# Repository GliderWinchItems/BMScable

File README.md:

# BMScable
Battery Management System cable tester.

Based on the ST's Nucleo 446R, this unit tests the battery module cable connector and wiring for correct voltages before using it with the BMS unit.

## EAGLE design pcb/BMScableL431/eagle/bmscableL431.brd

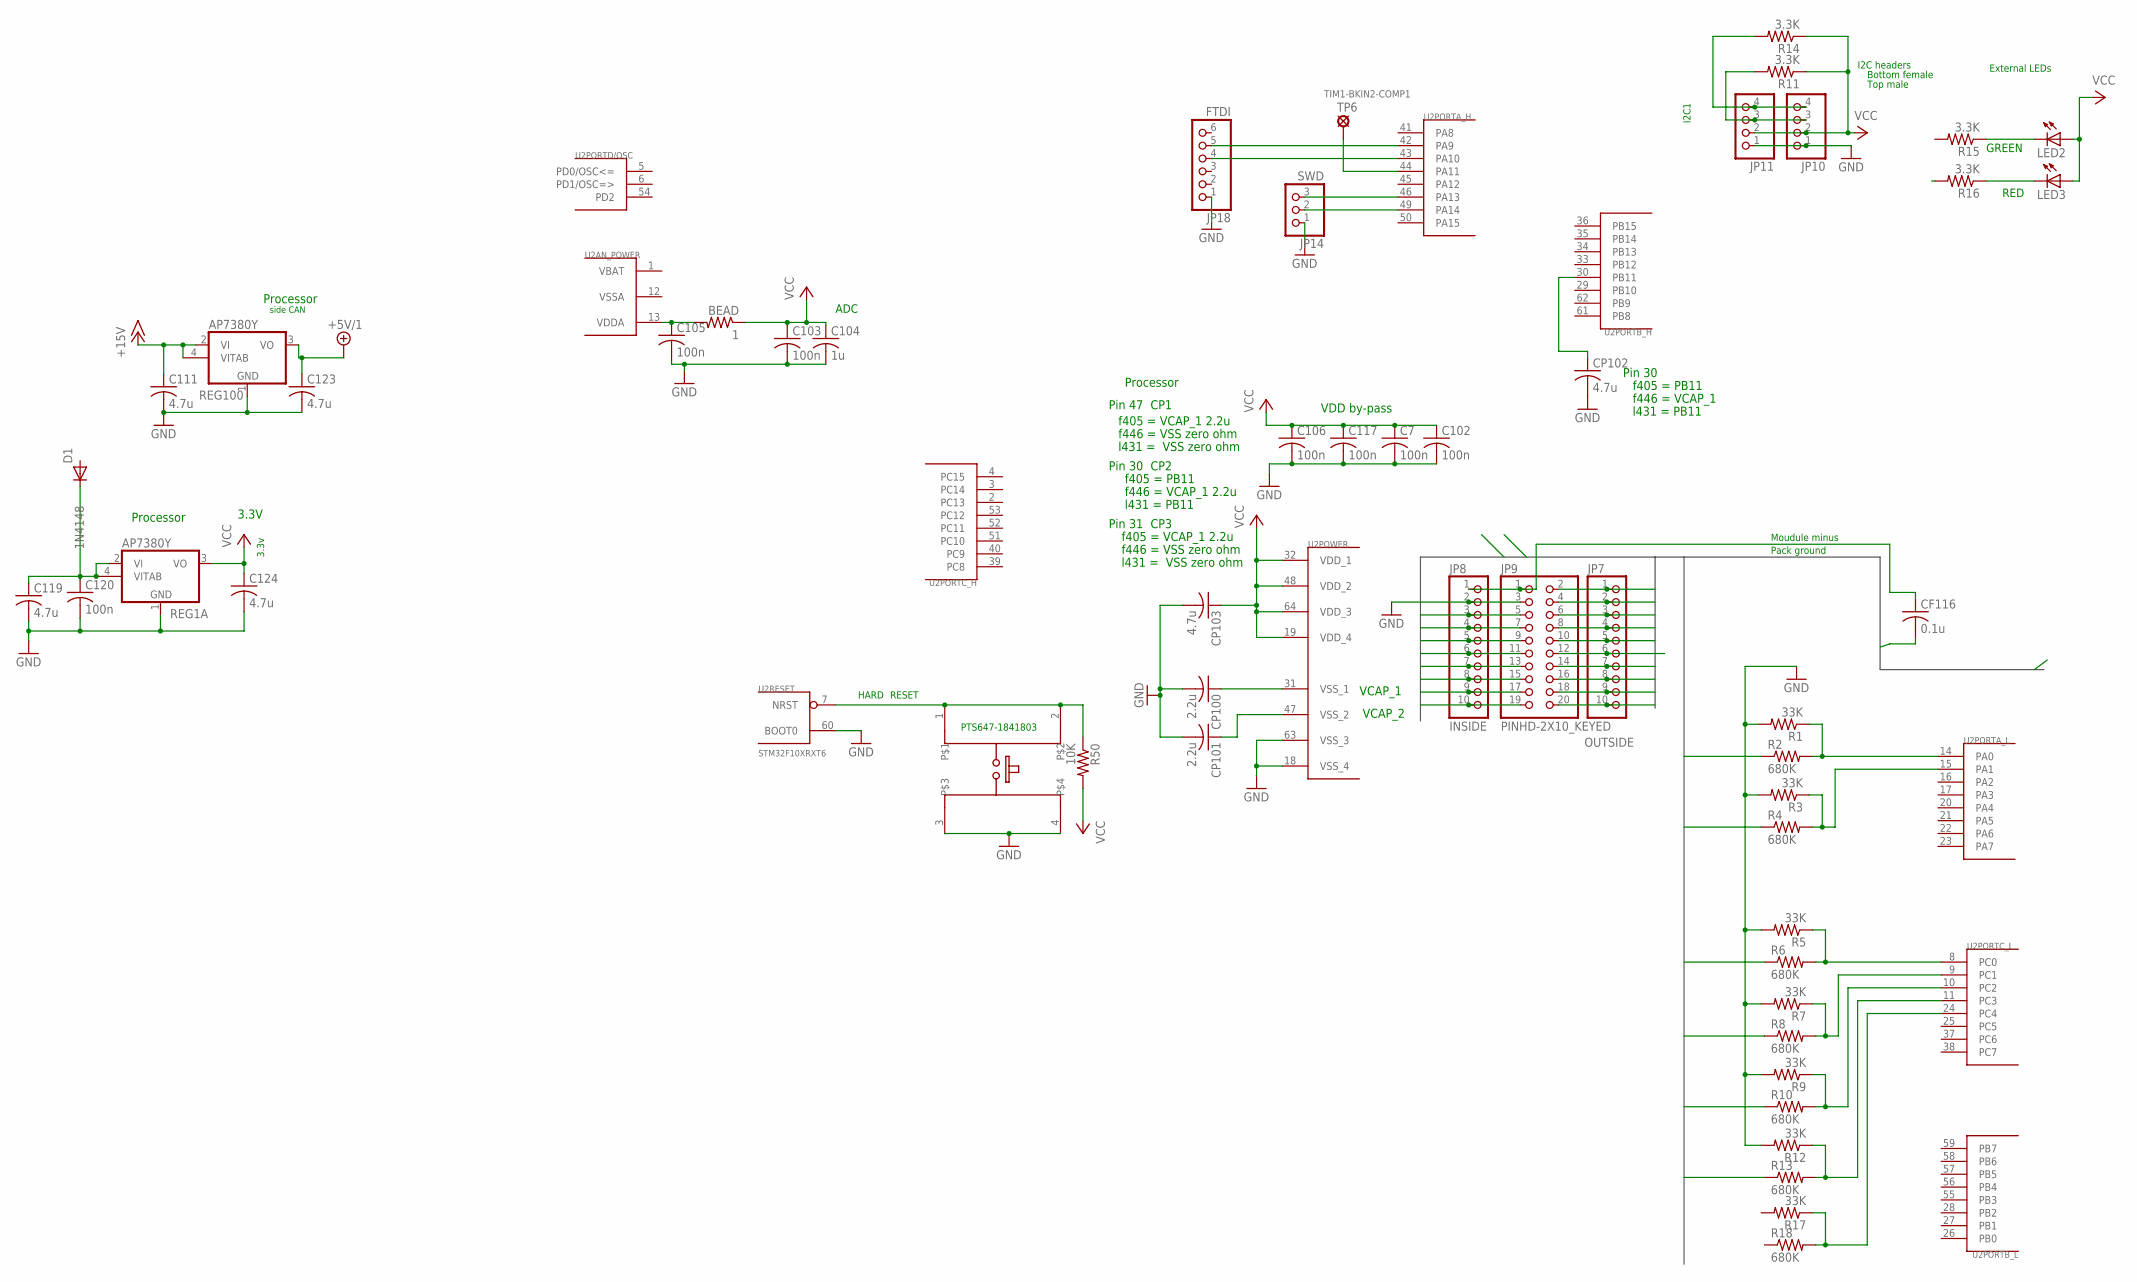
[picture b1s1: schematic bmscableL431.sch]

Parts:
BEAD: 1; R0603
C7, C102, C103, C105, C106, C117, C120: 100n; C0603
C104: 1u; C0603
C111, C119, C123: 4.7u; C0603
C124: 4.7u; C0805
CF116: 0.1u; C0603
CP100, CP101: 2.2u; C0603
CP102, CP103: 4.7u; C0603
D1: 1N4148; DO41-10_VERT
JP7: OUTSIDE; 1X10
JP8: INSIDE; 1X10
JP9: PINHD-2X10_KEYED; 2X10_KEYED
JP10, JP11: PINHD-1X4; 1X04
JP14: SWD; 1X03
JP18: FTDI; 1X06
LED2, LED3: LEDCHIP-LED0603; CHIP-LED0603
R1, R3, R5, R7, R9, R12, R17: 33K; R0603
R2, R4, R6, R8, R10, R13, R18: 680K; R0603
R11, R14, R15, R16: 3.3K; R0603
R50: 10K; R0603
REG1A, REG100: AP7380Y; SOT89
TP6: SOLDPAD0.6MM; SOLPAD.6MM
U2: STM32F10XRXT6; TQFP64
U$1: E-SWITCH2

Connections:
+5V/1: C123.1, REG100.3 (VO)
+15V: C111.1, REG100.2 (VI), REG100.4 (VITAB)
C0: JP7.2, JP9.4
C1: JP8.7, JP9.13
C2: JP8.3, JP9.5
C3: JP7.7, JP9.14, R4.1
C4: JP7.3, JP9.6
C5: JP8.8, JP9.15, R2.1
C6: JP8.4, JP9.7
C7: JP7.8, JP9.16, R13.1
C8: JP7.4, JP9.8
C9: JP8.9, JP9.17, R10.1
C10: JP8.5, JP9.9
C11: JP7.9, JP9.18, R8.1
C12: JP7.5, JP9.10
C13: JP8.10, JP9.19, R6.1
C14: JP8.6, JP9.11
C15: JP7.10, JP9.20
C16: JP7.6, JP9.12
GND: C7.2, C102.2, C103.2, C104.2, C105.2, C106.2, C111.2, C117.2, C119.2, C120.2, C123.2, C124.2, CP100.2, CP101.2, CP102.2, CP103.2, JP8.2, JP9.3, JP10.1, JP11.1, JP14.1, JP18.1, R1.2, R3.2, R5.2, R7.2, R9.2, R12.2, REG1A.1 (GND), REG100.1 (GND), U2.18 (VSS_4), U2.60 (BOOT0), U2.63 (VSS_3), U$1.3, U$1.4
LED-EXT-GRN-CATHODE: LED2.C, R15.1
LED-EXT-RED-CATHODE: LED3.C, R16.1
NRST: R50.1, U2.7 (NRST), U$1.1, U$1.2
PA0-C5-IN5: R1.1, R2.2, U2.14 (PA0)
PA1-C3-IN6: R3.1, R4.2, U2.15 (PA1)
PA9-USART1-TX: JP18.5, U2.42 (PA9)
PA10-USART1-RX: JP18.4, U2.43 (PA10)
PA13-SWDIO: JP14.3, U2.46 (PA13)
PA14-SWCLK: JP14.2, U2.49 (PA14)
PB1-LED-RED: R16.2
PB6-I2C1-SCL: JP10.4, JP11.4, R14.2
PB7-I2C2-SDA: JP10.3, JP11.3, R11.2
PB11-I2C2-SDA|VCAP1: CP102.1, U2.30 (PB11)
PC0-C13-IN1: R5.1, R6.2, U2.8 (PC0)
PC1-C11-IN2: R7.1, R8.2, U2.9 (PC1)
PC2-C9-IN3: R9.1, R10.2, U2.10 (PC2)
PC3-C7-IN4: R12.1, R13.2, U2.11 (PC3)
PC4-CX-IN13: R17.1, R18.2, U2.24 (PC4)
PGND_SRN_V: CF116.1, JP8.1, JP9.1
SRP: CF116.2, JP7.1, JP9.2
TIM1_BKIN2_COMP2: TP6.MP, U2.44 (PA11)
V-ORED: C119.1, C120.1, D1.C, REG1A.2 (VI), REG1A.4 (VITAB)
VBAT: U2.1 (VBAT)
VCC: BEAD.1, C7.1, C102.1, C103.1, C104.1, C106.1, C117.1, C124.1, CP103.1, JP10.2, JP11.2, LED2.A, LED3.A, R11.1, R14.1, R50.2, REG1A.3 (VO), U2.19 (VDD_4), U2.32 (VDD_1), U2.48 (VDD_2), U2.64 (VDD_3)
VDDA1: BEAD.2, C105.1, U2.13 (VDDA)
VSSA: U2.12 (VSSA)
VSS_1-VCAP_1: CP100.1, U2.31 (VSS_1)
VSS_3: CP101.1, U2.47 (VSS_2)

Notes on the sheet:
RESET
HARD
3.3V
VCAP_1
VCAP_2
Pin 47
f405 = VCAP_1 2.2u
Pin 30
f446 = VCAP_1 2.2u
Pin 31
f446 = VSS zero ohm
CP1
CP3
f405 = PB11
f446 = VCAP_1
CP2
ADC
GREEN
RED
I2C headers
Bottom female
3.3v
Processor
PTS647-1841803
Moudule minus
Pack ground
External LEDs
side CAN
TIM1-BKIN2-COMP1
l431 = VSS zero ohm
l431 = PB11
VDD by-pass
Top male
I2C1

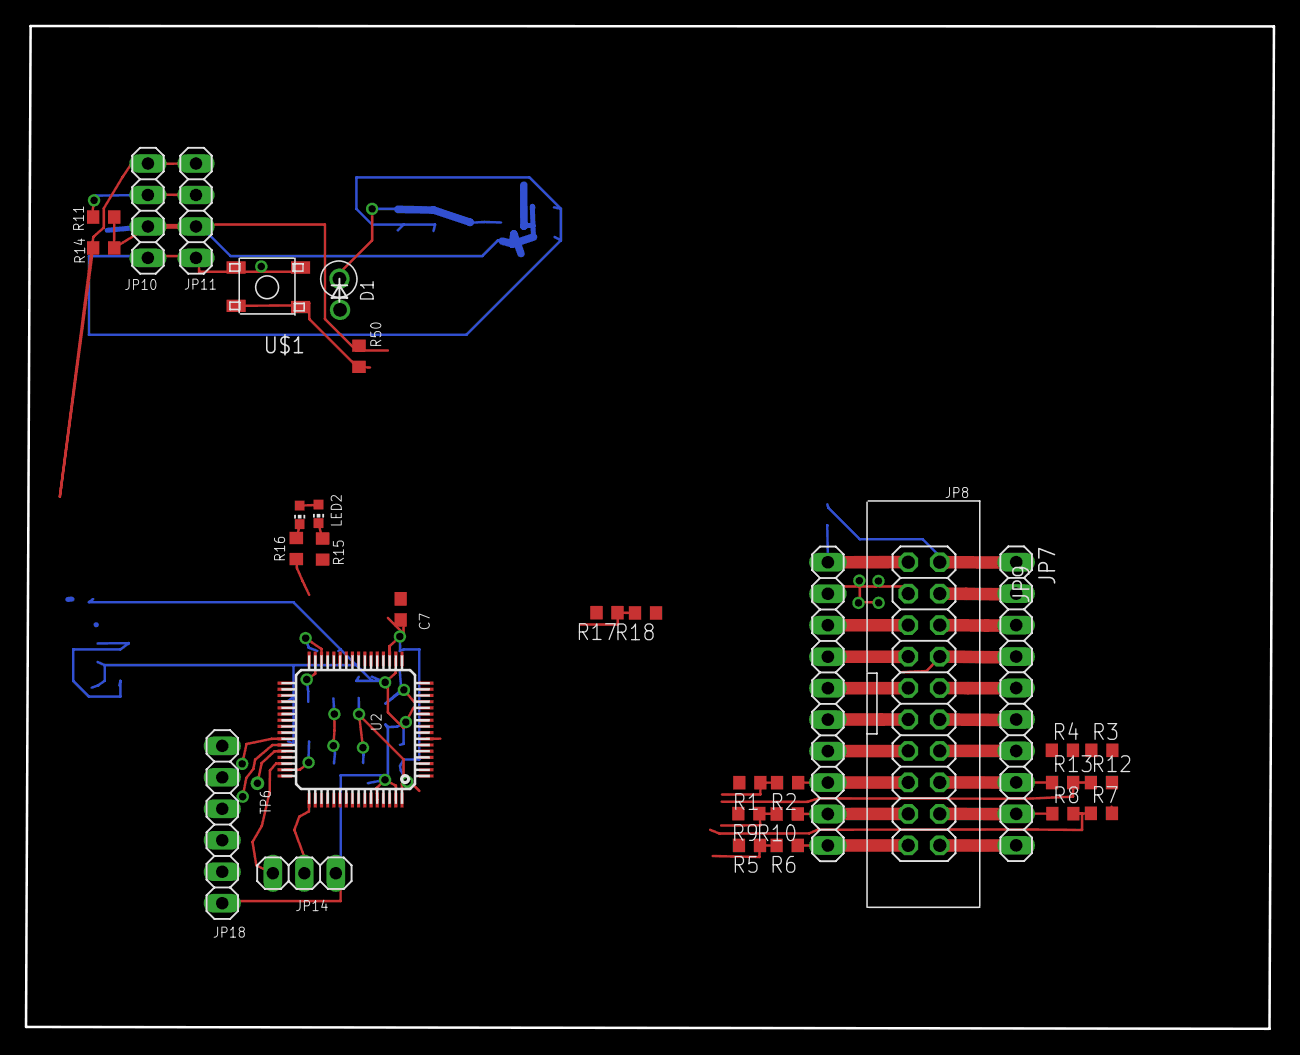
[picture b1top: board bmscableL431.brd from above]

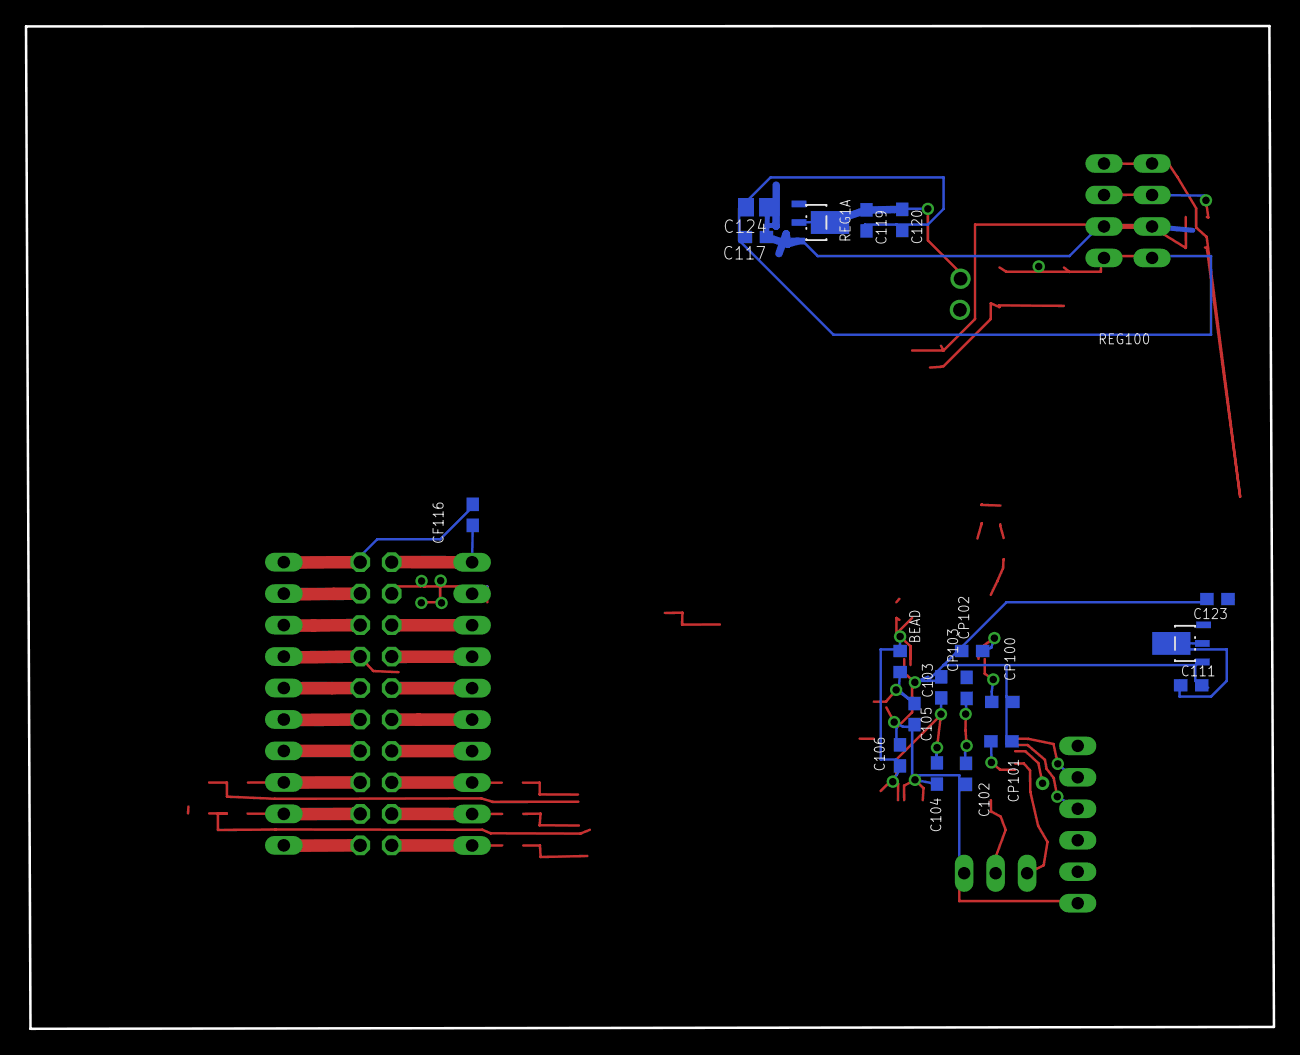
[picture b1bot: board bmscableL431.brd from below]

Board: 2 copper layers, 100.7 x 81.0 mm, 52 parts (19 on the bottom side), 45 nets.

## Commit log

2020-07-25 getting started with BMS cable tester using Nucleo board
2020-07-26 save work
2020-07-30 updating
2020-11-23 add datasheet and txt file
2020-11-23 add datasheet
2020-11-26 update to initial MX config
2020-11-26 update perfboard wiring
2020-11-27 update wiring
2020-11-29 backup work
2021-02-24 pcb design and layout, first cut.
2021-02-25 add eagleNucleo. Optional L431 or Nucleo for processorizing it.
2021-02-26 pcb Nucleo nearing completion. Renumbered parts
2021-02-26 clean out eagle backup files
2021-02-26 bmscableNucleo layout cleanup.
2021-02-27 added Nucleo to header for CAN, I2C1. Added Schottky diodes for reverse protection. Added numbers to cell vias
2021-02-28 Added polarity LEDs, ISO1042 CAN driver, spare fet
2021-03-02 bmscableNucleo.docx update
2021-04-25 Added caps for RC filtering. PB6,7 for I2C1 to Nucleo. GRN-RED led to Nucleo changed to PC10,11. Added hole for User pushbutton but it is under FTDI, when FTDI mounted horizontal. Cosmetic items to F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
2021-04-26 Added missing FET gate, PB2 to Nucleo header connection. Added pcb reset to Nucleo RESET. Cleaned up some large font labels
2021-05-28 Add gerber zip
2021-07-30 add STM32L431 openocd notes
2021-08-03 Begin sw development. morse.c working. yprintf not.
2021-08-07 backup progress.
2021-08-09 backup work. adc filtering working
2021-08-13 update work
2021-08-17 back and save work. Calibrating board #1. Revised ADC scan sequence so mapping is not needed.
2021-08-18 added external charger fet on-off
2021-08-21 update and backup work.
2021-08-24 save and backup
2022-03-24 update ribbon colors
